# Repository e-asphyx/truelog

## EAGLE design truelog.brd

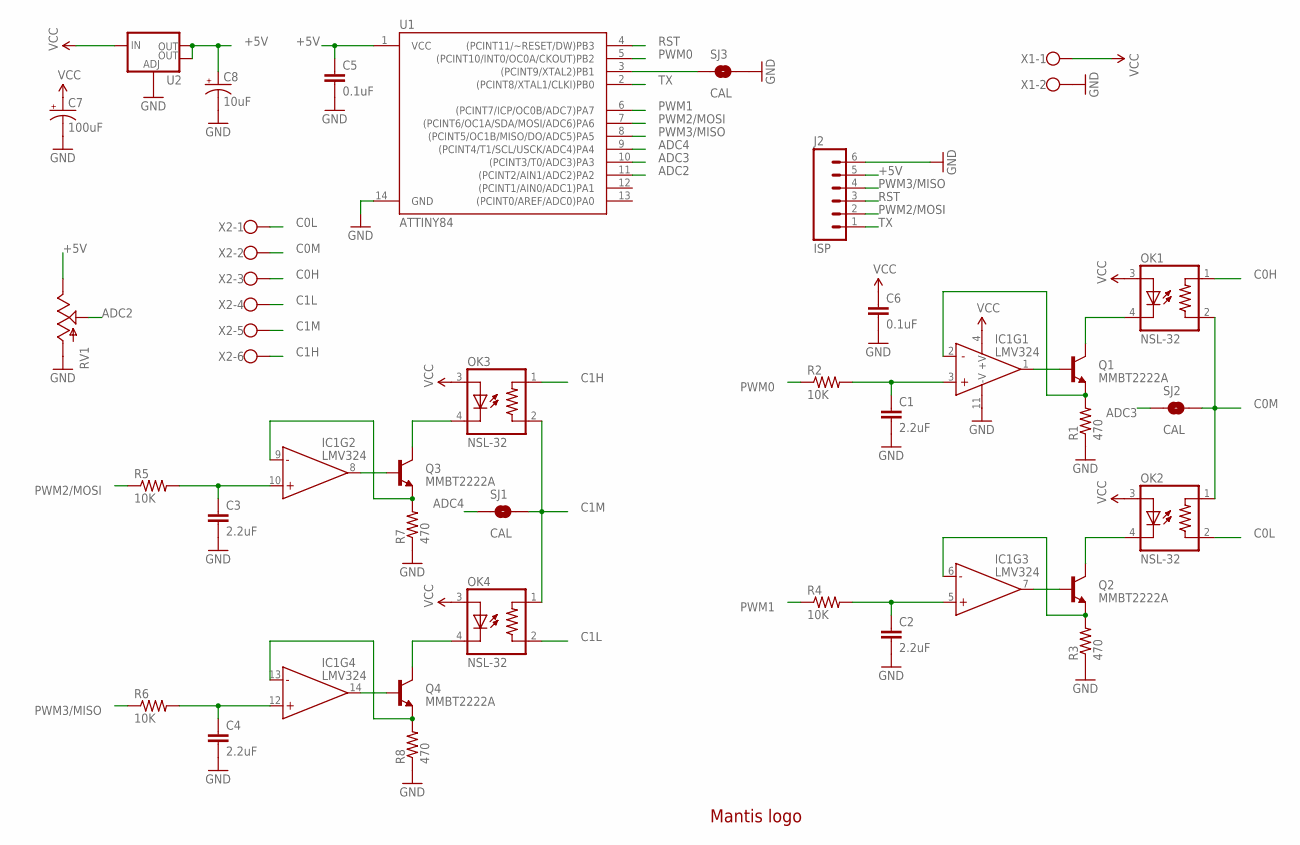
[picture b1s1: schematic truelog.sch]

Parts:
C1, C2, C3, C4: 2.2uF; 0805-CAP
C5, C6: 0.1uF; 0603-CAP
C7: 100uF; PANASONIC_D
C8: 10uF; PANASONIC_C
IC1: LMV324; SO014
J2: ISP; 1X06_LOCK
LOGO1: LOGO-MANTIS
OK1, OK2, OK3, OK4: NSL-32; NSL-OK
Q1, Q2, Q3, Q4: MMBT2222A; SOT23-3
R1, R3, R7, R8: 470; 0805
R2, R4, R5, R6: 10K; 0603-RES
RV1: POT; ALPS_POT
SJ1, SJ2, SJ3: CAL; SJ_2S-NO
U1: ATTINY84; SO14
U2: V_REG_LM1117SOT223; SOT223
X1: W237-102
X2: W237-136

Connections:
+5V: C5.1, C8.+, J2.5, RV1.P$1 (E), U1.1 (VCC), U2.2 (OUT), U2.4 (OUT)
ADC2: RV1.P$2 (S), U1.11 ((PCINT2/AIN1/ADC2)PA2)
ADC3: SJ2.1, U1.10 ((PCINT3/T0/ADC3)PA3)
ADC4: SJ1.1, U1.9 ((PCINT4/T1/SCL/USCK/ADC4)PA4)
C0H: OK1.1 (R0), X2.3
C0L: OK2.2 (R1), X2.1
C0M: OK1.2 (R1), OK2.1 (R0), SJ2.2, X2.2
C1H: OK3.1 (R0), X2.6
C1L: OK4.2 (R1), X2.4
C1M: OK3.2 (R1), OK4.1 (R0), SJ1.2, X2.5
GND: C1.2, C2.2, C3.2, C4.2, C5.2, C6.2, C7.-, C8.-, IC1.11 (-V), J2.6, R1.1, R3.1, R7.1, R8.1, RV1.P$3 (A), SJ3.2, U1.14 (GND), U2.1 (ADJ), X1.2
unnamed: SJ3.1, U1.3 ((PCINT9/XTAL2)PB1)
unnamed: OK1.4 (C), Q1.3 (C)
unnamed: IC1.2 (-IN), Q1.2 (E), R1.2
unnamed: C1.1, IC1.3 (+IN), R2.2
unnamed: IC1.1 (OUT), Q1.1 (B)
unnamed: IC1.7 (OUT), Q2.1 (B)
unnamed: IC1.8 (OUT), Q3.1 (B)
unnamed: OK2.4 (C), Q2.3 (C)
unnamed: OK3.4 (C), Q3.3 (C)
unnamed: OK4.4 (C), Q4.3 (C)
unnamed: IC1.6 (-IN), Q2.2 (E), R3.2
unnamed: C2.1, IC1.5 (+IN), R4.2
unnamed: C3.1, IC1.10 (+IN), R5.2
unnamed: C4.1, IC1.12 (+IN), R6.2
unnamed: IC1.14 (OUT), Q4.1 (B)
unnamed: IC1.9 (-IN), Q3.2 (E), R7.2
unnamed: IC1.13 (-IN), Q4.2 (E), R8.2
PWM0: R2.1, U1.5 ((PCINT10/INT0/OC0A/CKOUT)PB2)
PWM1: R4.1, U1.6 ((PCINT7/ICP/OC0B/ADC7)PA7)
PWM2/MOSI: J2.2, R5.1, U1.7 ((PCINT6/OC1A/SDA/MOSI/ADC6)PA6)
PWM3/MISO: J2.4, R6.1, U1.8 ((PCINT5/OC1B/MISO/DO/ADC5)PA5)
RST: J2.3, U1.4 ((PCINT11/~RESET/DW)PB3)
TX: J2.1, U1.2 ((PCINT8/XTAL1/CLKI)PB0)
VCC: C6.1, C7.+, IC1.4 (+V), OK1.3 (A), OK2.3 (A), OK3.3 (A), OK4.3 (A), U2.3 (IN), X1.1

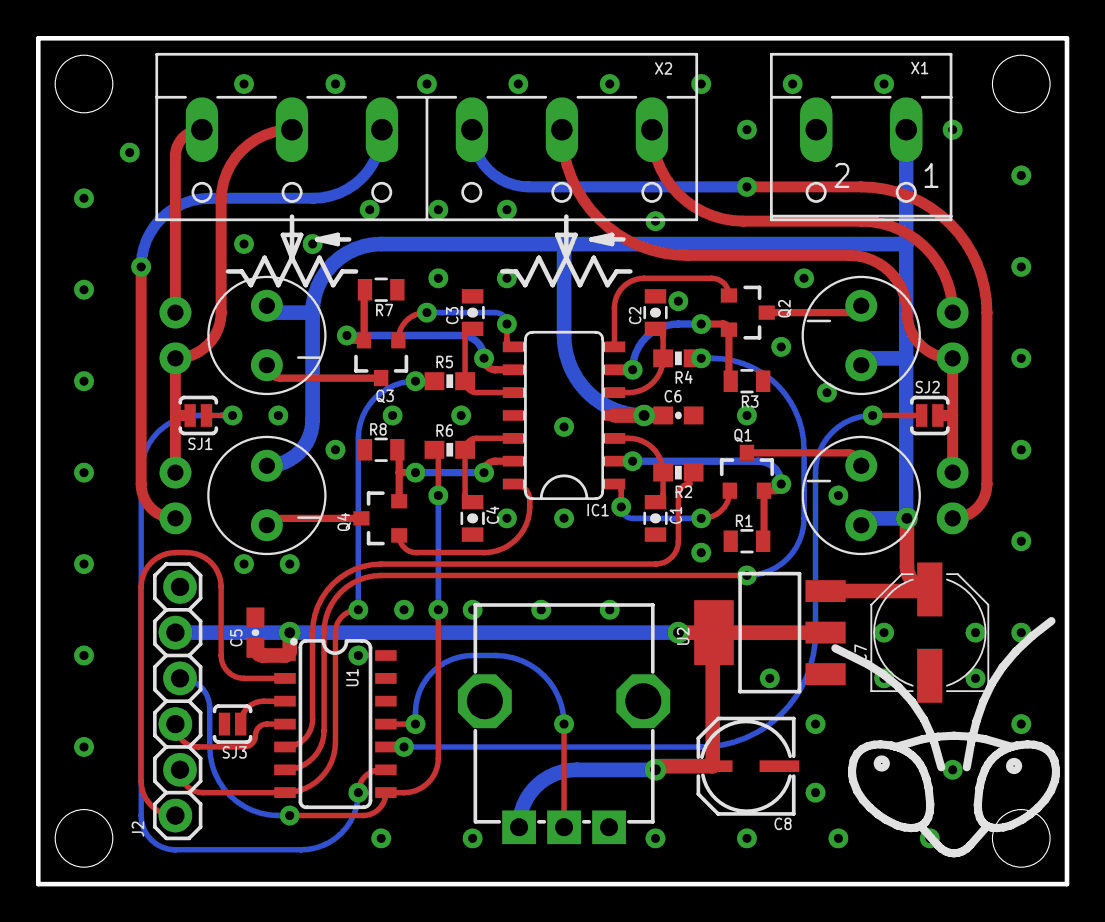
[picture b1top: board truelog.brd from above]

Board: 2 copper layers, 57.1 x 47.0 mm, 37 parts (0 on the bottom side), 35 nets.

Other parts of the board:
U$1, U$2: POT-SYMBOL

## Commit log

2016-09-26 Initial
2016-09-26 PCB eye candy
2016-09-26 PDFs
2016-09-26 Logo added

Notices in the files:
parts and their libraries:
SparkFun-Capacitors: Licensing: Creative Commons ShareAlike 4.0 International - https://creativecommons.org/licenses/by-sa/4.0
